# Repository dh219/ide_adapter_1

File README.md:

# ide_adapter_1

44-pin 2mm pitch IDE host to two device adapter supporting cable select with optional physical byte swap header

## Atari Falcon

This adapter is intended for use in my Atari Falcon which has an 44-pin 2mm-pitch IDE connection soldered to the board with only one connector for a hard disc.

This allows two discs to be added to the Falcon, if they support running in master/slave configuration, either via jumpers on the discs, or via cable select, which this board supports.

## Byte Swap

This board also has an additional byte-swapped host header, which a suitable hard disc driver on the atari can make use of for faster interoperability with modern machines.

## Youtube

My video demonstrating this and assembing it can be found here https://www.youtube.com/watch?v=6OSfqDosSyg

## PCBWay

I have A PCBWay Profile where you may find & order this project: https://www.pcbway.com/project/member/?bmbno=2C89C44C-EDF4-43

Copyright 2023 D Henderson, released under the terms of the GPLv2

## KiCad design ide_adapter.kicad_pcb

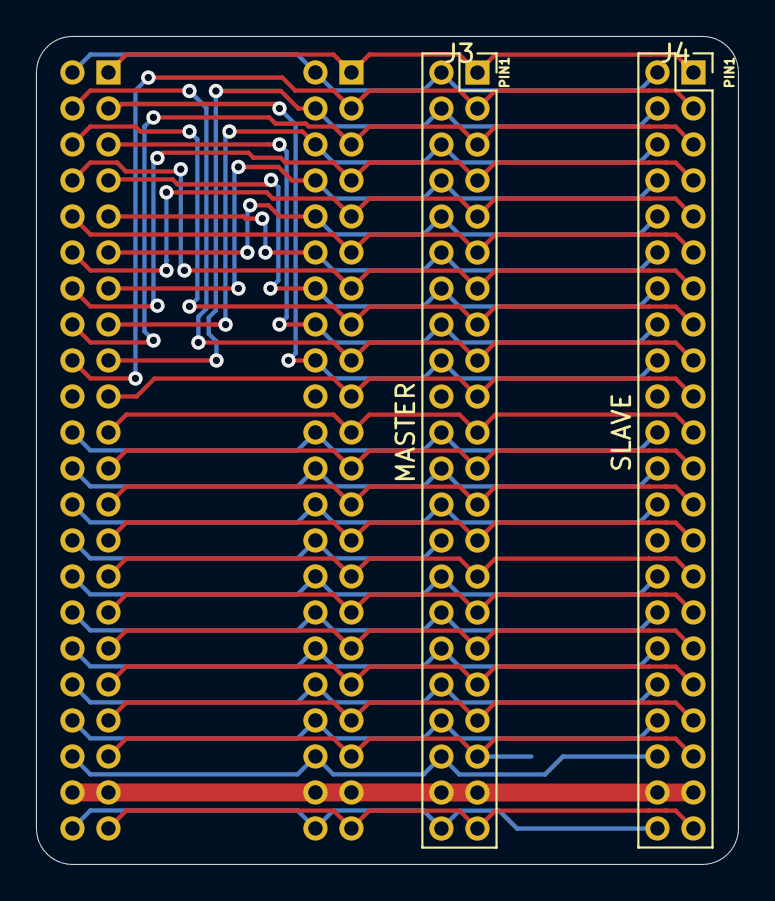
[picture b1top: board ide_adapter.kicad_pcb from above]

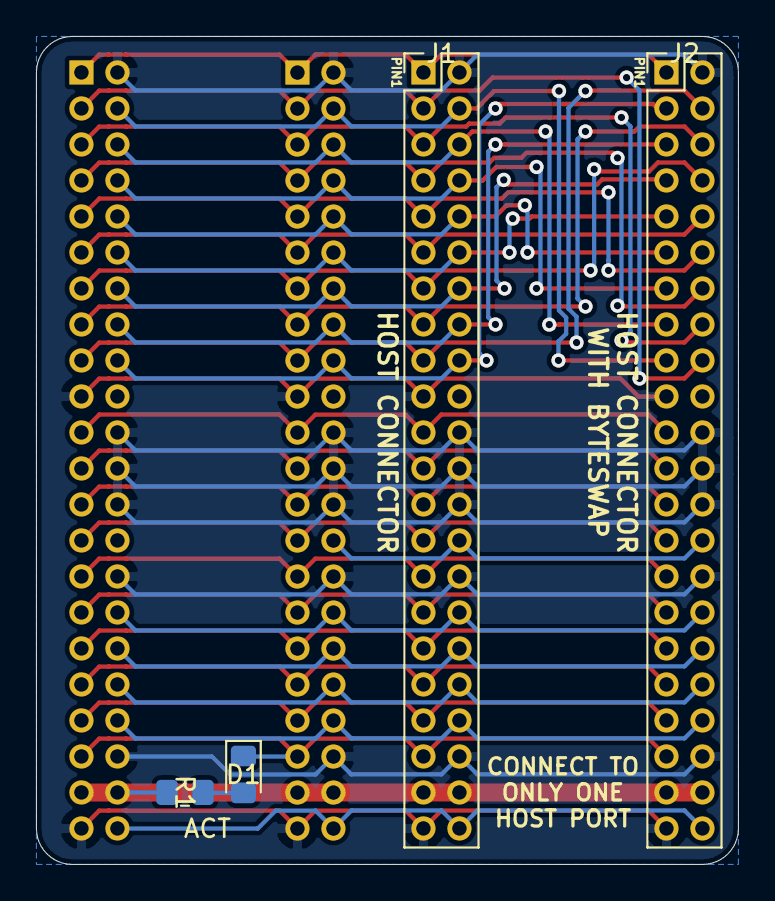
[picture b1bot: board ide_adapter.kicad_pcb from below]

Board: 2 copper layers, 39.0 x 46.0 mm, 6 parts (4 on the bottom side), 36 nets.

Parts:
D1: LED; LED_0805_2012Metric_Pad1.15x1.40mm_HandSolder
J1, J2: PATA-44_Host; PinHeader_2x22_P2.00mm_Vertical
J3, J4: PATA-44_Drive; PinSocket_2x22_P2.00mm_Vertical
R1: 1k; R_0805_2012Metric_Pad1.20x1.40mm_HandSolder

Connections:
+5V: J1.41, J1.42, J2.41, J2.42, J3.41, J3.42, J4.41, J4.42, R1.2
/CSEL: J1.28, J2.28, J3.28
/DA0: J1.35, J2.35, J3.35, J4.35
/DA1: J1.33, J2.33, J3.33, J4.33
/DA2: J1.36, J2.36, J3.36, J4.36
/DD0: J1.17, J2.4, J3.17, J4.17
/DD1: J1.15, J2.6, J3.15, J4.15
/DD2: J1.13, J2.8, J3.13, J4.13
/DD3: J1.11, J2.10, J3.11, J4.11
/DD4: J1.9, J2.12, J3.9, J4.9
/DD5: J1.7, J2.14, J3.7, J4.7
/DD6: J1.5, J2.16, J3.5, J4.5
/DD7: J1.3, J2.18, J3.3, J4.3
/DD8: J1.4, J2.17, J3.4, J4.4
/DD9: J1.6, J2.15, J3.6, J4.6
/DD10: J1.8, J2.13, J3.8, J4.8
/DD11: J1.10, J2.11, J3.10, J4.10
/DD12: J1.12, J2.9, J3.12, J4.12
/DD13: J1.14, J2.7, J3.14, J4.14
/DD14: J1.16, J2.5, J3.16, J4.16
/DD15: J1.18, J2.3, J3.18, J4.18
/DMARQ: J1.21, J2.21, J3.21, J4.21
/INTRQ: J1.31, J2.31, J3.31, J4.31
/IORDY: J1.27, J2.27, J3.27, J4.27
/PDIAG: J1.34, J2.34, J3.34, J4.34
/~CS0: J1.37, J2.37, J3.37, J4.37
/~CS1: J1.38, J2.38, J3.38, J4.38
/~DIOR: J1.25, J2.25, J3.25, J4.25
/~DIOW: J1.23, J2.23, J3.23, J4.23
/~DMACK: J1.29, J2.29, J3.29, J4.29
/~IOCS16: J1.32, J2.32, J3.32, J4.32
/~LED: D1.1, J1.39, J2.39, J3.39, J4.39
/~RESET: J1.1, J2.1, J3.1, J4.1
/~TYPE: J1.44, J2.44, J3.44, J4.44
GND: J1.2, J1.19, J1.22, J1.24, J1.26, J1.30, J1.40, J1.43, J2.2, J2.19, J2.22, J2.24, J2.26, J2.30, J2.40, J2.43, J3.2, J3.19, J3.22, J3.24, J3.26, J3.30, J3.40, J3.43, J4.2, J4.19, J4.22, J4.24, J4.26, J4.30, J4.40, J4.43
unnamed: D1.2, R1.1

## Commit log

2023-04-05 Initial file commit
